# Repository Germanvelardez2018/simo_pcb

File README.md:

# Simo pcb

## Proyecto en construccion.

<h2>
    Diseño y construccion de PCB de conexion para el dispositivo drifter modular SIMO (Sistema de Monitoreo).
</h2>

## Diseñador: German Velardez

### Breve resumen del proyecto a realizar:

El proyecto consiste en el diseño y prueba de concepto de un dispositivo tipo drifter basado en una placa de desarrollo y modulos tipo arduino.
Para realizar la conexion de los distintos elementos se diseñara dos placas PCB:
*  **Simo Shield** (dentro de carpeta simo_shield)
*  **Simo Bateria** (dentro de carpeta sdimo_bateria)

## Simo Shield
 PCB para interconectar los siguientes elementos:
  * **Placa de desarrollo basada en STM33F103xx** (Bluepill)
      <div align="center" >
     
     </div>

  *  **Modulo comunicacion 4G  diseñado por Elemon** (EESA-IOT SIM7000G PLACA SHIELD 2G/CAT-M1/NB1/GNSS)
      <div align="center" >
       
       </div>
  *  **Sensor acelerometro** (MPU6050)
     <div align="center" >
       
       </div>
  *  **Memoria flash externa para almacenar datos** (AT45DB)
     <div align="center" >
       
       </div>
  *  **Conector para acceso a puerto UART de debug**
     <div align="center" >
       
       </div>

## Simo Bateria
 Este PBC tiene como objetivo gestionar los elementos necesarios para que el dispositivo pueda funcionar con Baterias.
 PBC para interconectar los siguientes elementos:
 * **2 porta baterias 18650**
 * **Regulador Step Down (LM2596S)**
 * **Conectores de salida varios**

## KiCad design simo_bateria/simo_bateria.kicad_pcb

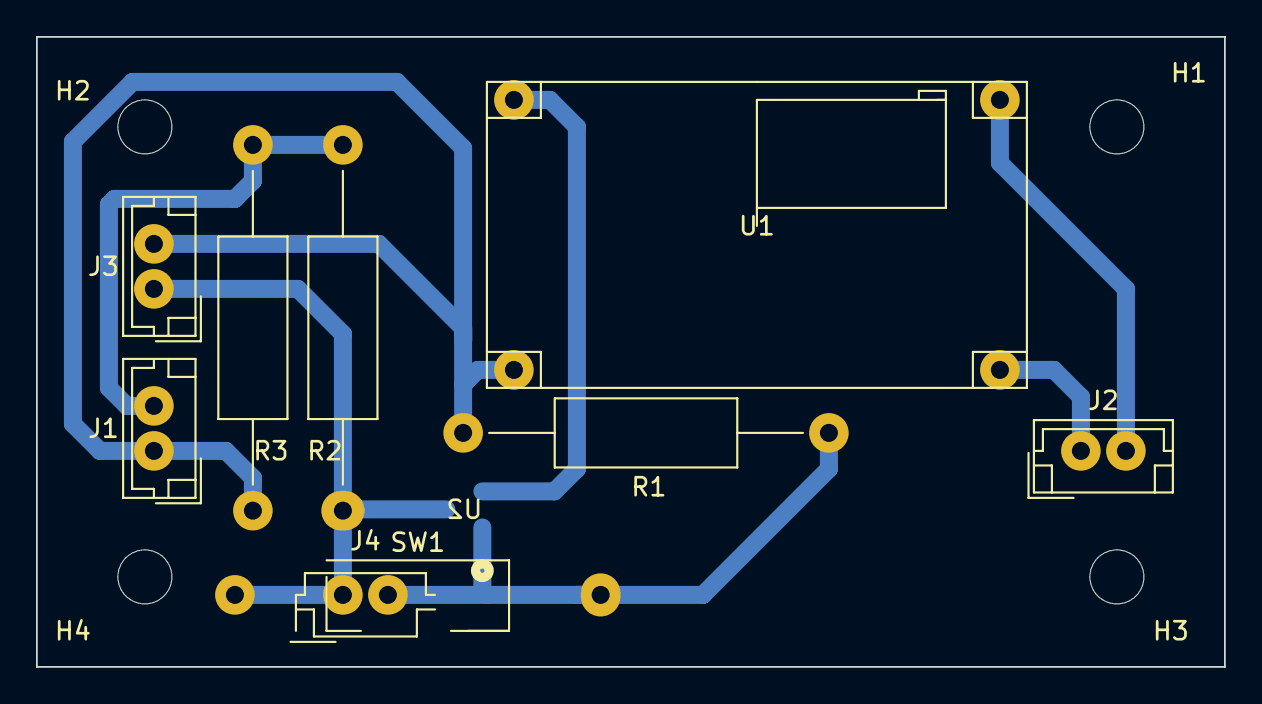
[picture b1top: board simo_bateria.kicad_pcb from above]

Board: 2 copper layers, 66.0 x 35.0 mm, 14 parts (1 on the bottom side), 7 nets.

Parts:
H1, H2, H3, H4: MountingHole; MountingHole_3mm
J1: BAT_LEVEL; JST_EH_B2B-EH-A_1x02_P2.50mm_Vertical
J2: Plugin; JST_EH_B2B-EH-A_1x02_P2.50mm_Vertical
J3: VBAT IN; JST_EH_B2B-EH-A_1x02_P2.50mm_Vertical
J4: SWD; JST_EH_B2B-EH-A_1x02_P2.50mm_Vertical
R1: 10k; RESITOR_THT
R2: 355k; RESITOR_THT
R3: 155k; RESITOR_THT
SW1: SW_Reed; RESITOR_THT
U1: mod_mt3608; mt3608_v2
U2: BSS314PEH6327XTSA1; TRANS_BSS314PEH6327XTSA1_INF

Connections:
GND: J1.1, J3.2, R1.2, R3.2, U1.2 (VIN-)
unnamed: J1.2, R2.1, R3.1
unnamed: J2.1, U1.4 (VOUT-)
unnamed: J2.2, U1.3 (VOUT+)
unnamed: J3.1, J4.1, R2.2, SW1.1, U2.3
unnamed: J4.2, R1.1, SW1.2, U2.1
unnamed: U1.1 (VIN+), U2.2

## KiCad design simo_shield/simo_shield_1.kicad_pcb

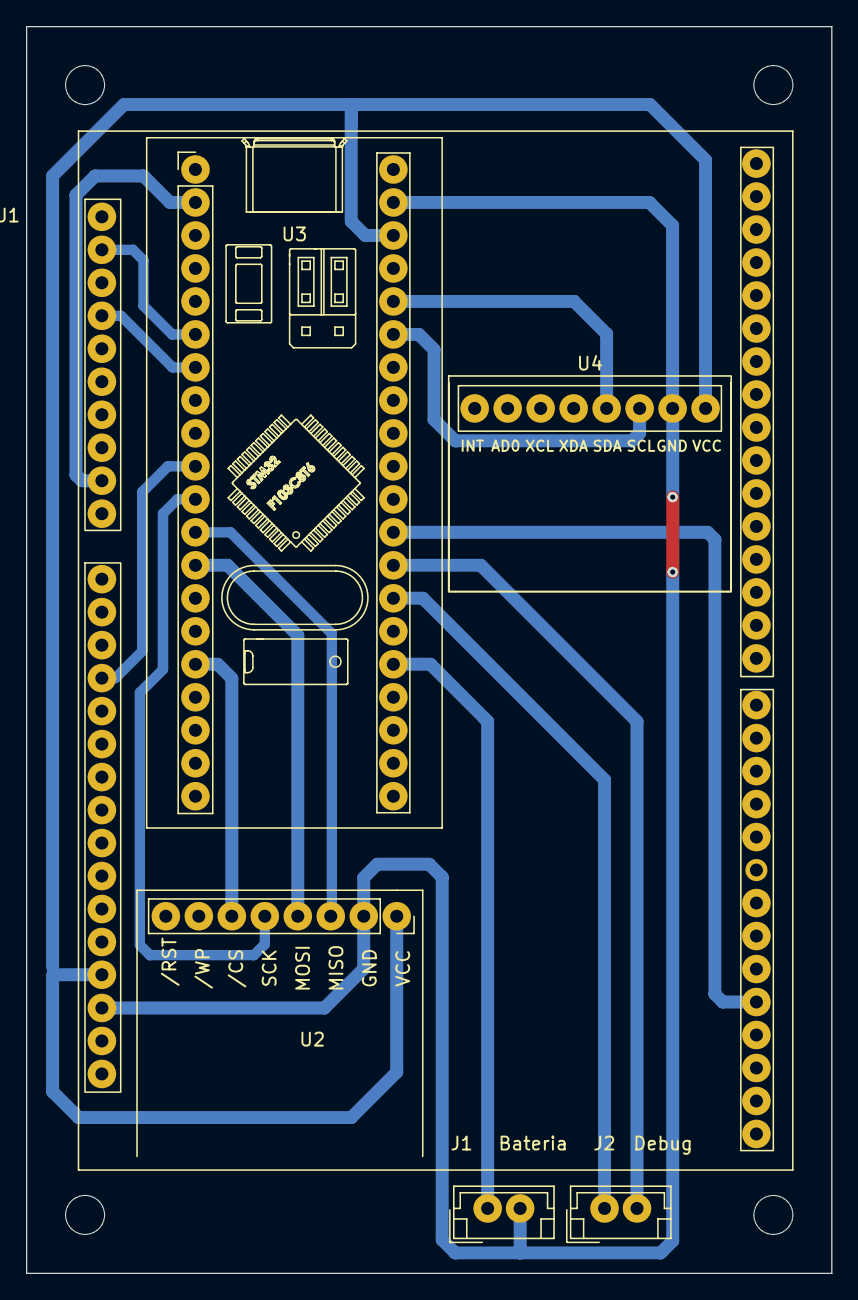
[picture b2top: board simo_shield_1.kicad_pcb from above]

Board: 2 copper layers, 62.0 x 96.0 mm, 10 parts (0 on the bottom side), 16 nets.

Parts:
H1, H2, H3, H4: MountingHole; MountingHole_3mm
J1: Conector nivel de bateria; JST_EH_B2B-EH-A_1x02_P2.50mm_Vertical
J2: Conector para debug; JST_EH_B2B-EH-A_1x02_P2.50mm_Vertical
U1: elemon_board; elemon_board_compacto
U2: modulo_flash_externa; conector_flash_ext
U3: bluepill_board_stm32; YAAJ_BluePill_SWD_1_modificado
U4: modulo_acelerometro; MPU6050

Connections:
+3.3V: U1.23 (USB33), U2.1 (VCC), U3.38 (3V3), U4.8 (VCC)
/BAT_ENA_PIN: U1.52 (BAT_ENA), U3.29 (PA4)
/UART_DEBUG_RX: J2.1, U3.27 (PA2)
/UART_DEBUG_TX: J2.2, U3.28 (PA3)
GND: J1.2, U1.24 (GND), U2.2 (GND), U3.39 (GND), U4.7 (GND)
unnamed: J1.1, U3.25 (PA0)
unnamed: U1.2 (SER3_RX), U3.6 (PA9)
unnamed: U1.4 (SER3_TX), U3.7 (PA10)
unnamed: U1.9 (PWRKEY), U3.2 (PB13)
unnamed: U1.14 (RI), U3.10 (PA15)
unnamed: U2.3 (MISO), U3.12 (PB4)
unnamed: U2.4 (MOSI), U3.13 (PB5)
unnamed: U2.5 (SCK), U3.11 (PB3)
unnamed: U2.6 (/CS), U3.16 (PB8)
unnamed: U3.35 (PB10), U4.6 (SCL)
unnamed: U3.36 (PB11), U4.5 (SDA)

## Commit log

2022-05-16 iniciamos el proyecto
2022-05-16 se agrego carpeta bluepill donde se agrupo archivos relacionados con la placa de desarrollo bluepill
2022-05-16 modificaciones en elemon_board symbol
2022-05-17 organizando proyectos en carpetas: 2 proyectos , simo_shield (principal) y simo_bateria
2022-05-17 se completaron todos los modelos 3d y se verifico las footprint
2022-05-17 se hizo mas compacta pcb shield
2022-05-19 se agrego conector de bateria a ambas placas
2022-05-19 se guardaron modelos 3d de ambas placas en formato step
2022-05-19 update, se corrijio imagen step de simo_bateria
2022-05-31 se diseñaron las pistas de placa shield simo, revisar
2022-06-01 simo_bateria
2022-06-01 verifique conexiones en simo shield, todo ok.
2022-06-02 en esquematico pin 35 y 36 se conectan con SDA y SCL de MPU6050. En PCB no aparece tal conexion
2022-06-02 casi terminado, revisar PCB, error de conexion pero no entiendo por que.
2022-06-06 update en pcb shield
2022-06-06 simo shield pcb listo para revision
2022-06-06 se actualizo la placa bateria
2022-06-08 se agrego un circuito para mediciones de tension de bateria mediante la bluepill
2022-06-09 update a placas
2022-06-23 update simo_shield
2022-06-28 esquemas listos para revisar
2022-06-29 Creacion de readme basico
2022-06-29 Agregando carpeta con imagenes
2022-06-29 Se agregaron imagenes al repo
2022-06-29 Se agregaron mas imagenes
2022-06-29 update imagenes
2022-06-29 update placa simo bateria
2022-06-30 Se hizo refactory del proyecto simo_bateria
2022-06-30 update simo_bateria
2022-07-04 update en ambas placas. Cambio de formato de carpetas. Footprint asignado pero modelos 3d aun no.
2022-07-04 update en simo_bateria
2022-07-05 update en ambas placas, revision 02
2022-07-05 actualice el gitignore
2022-07-06 update 2. Listo para revision 2
2022-07-06 modificaciones menores en placa simo bateria. La salida del divisor de tension estaba mal ubicada.
2022-07-06 modificaciones en simo_shield: modulo_flash_externo
2022-07-07 update pcb:simo_bateria. Listo para segunda revision
2022-07-07 comenzamos el diseño del PCB de shield simo.
2022-07-11 simo shield: primer prototipo de pista terminado. 0 errores 26 warning. Todos por cortes en serigrafia
2022-07-13 simo_shield: Listo para primera revision de pcb
2022-07-14 update simo_shield pcb
2022-07-18 actualizacion en placa simo shield: correccion de inconsistencias en el modulo bluepill clone
2022-07-18 actualizacion de placa simo shield: se mejoro el ruteo y se agreggo plano de 3v3
2022-07-18 simo shield: se actualizo el numero de revision y fecha
2022-07-19 modificaciones en simo shield:Se modificaron los planos para enderezar los planos y se pulio detalles
2022-07-19 modificaciones simo shield: esquema y PCB. Detalle: se modifico la alimentacion y eliminaron conectores custom
2022-07-20 actualizaciones a pcb y esquema simo shield
2022-07-20 Placa simo bateria: Se modificaron conectores custom en esquema
2022-08-01 update simo_shield:pcb
2022-08-02 update simo_shiled: revision 3 de PCB
2022-08-04 Corregidos detalles en plano de Vcc y eliminada pista de GND en pin 39 del Bluepill.
2022-08-04 update: placa bateria, correccion de error en esquematico:GND de la salida LEVEL
2022-08-10 prueba de gitignore
2022-09-07 update: PINB13 paso a ser PA12. Modificar en firmware
2022-09-15 update pcb
2022-09-22 se hizo mas compacto el PCB
2022-10-03 update: pines de uart sim7000g conectados correctamente, mejor posicionamiento de memoria flash externa. PCB mas compacto
2022-10-04 modificaciones miniimas a esquematico para mejorar prolijidad
2022-10-04 modificaciones en pcb: se reposiciono sensor mpu6050,borneras y el pin de reset por software
2022-10-04 modificaciones en pcb
2023-04-18 modificaciones en el esquema simo-bateria
2023-04-18 update: cambios en esquematico simo bateria
2023-05-04 revision 3.0. Esquema. PCB con posicionamiento tentativo. Falta ver la posicion definitiva y mas conveniente del switch magnetico
2023-05-08 se agrego bornera para el switch magnetico. El pcb tengo 2 warnings a revisar
2023-05-31 Se efectuaron los siguientes cambios: - Corrección pista frente a conector J3. - Modificación de pista entre SW y R1.
2023-08-08 [Modificaciones] Reduccion de PCB para fabricar con CNC
2023-08-28 [SIMO_BATERIA] SE ELIMINO PLANO DE TIERRA
2023-08-28 [simo_bateria] Se elimino plano de tierra, faltaban archivos por actualizar
2023-08-28 [simo shield] Se elimino plano de tierra
2023-08-30 [simo shield] Se hicieron modificacion para fabricacion mediante CNC
2023-08-30 [simo bateria] Se realizaron modificaciones para fabricacion mediante CNC

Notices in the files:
simo_bateria/simo_bateria.kicad_pcb:
Licencia: CERN Open Hardware Licence version 2
